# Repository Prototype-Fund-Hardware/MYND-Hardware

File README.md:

# MYND loudspeaker 
This is a community repository (inofficial) for the open hardware of the Teufel loudspeaker MYND: https://teufel.de/mynd-107002004

Due to the file size, the STL files were not uploaded. They can be downloaded directly from the Teufel website: https://docs.teufel.de/download/MYND/open_source.zip

The repository for the firmware can be found here: https://github.com/teufelaudio/mynd-firmware

## License 
CC BY-SA 4.0 Copyright (c) 2025 Lautsprecher Teufel GmbH. 
The corresponding licenses can be found in the CAD and PCB folders.

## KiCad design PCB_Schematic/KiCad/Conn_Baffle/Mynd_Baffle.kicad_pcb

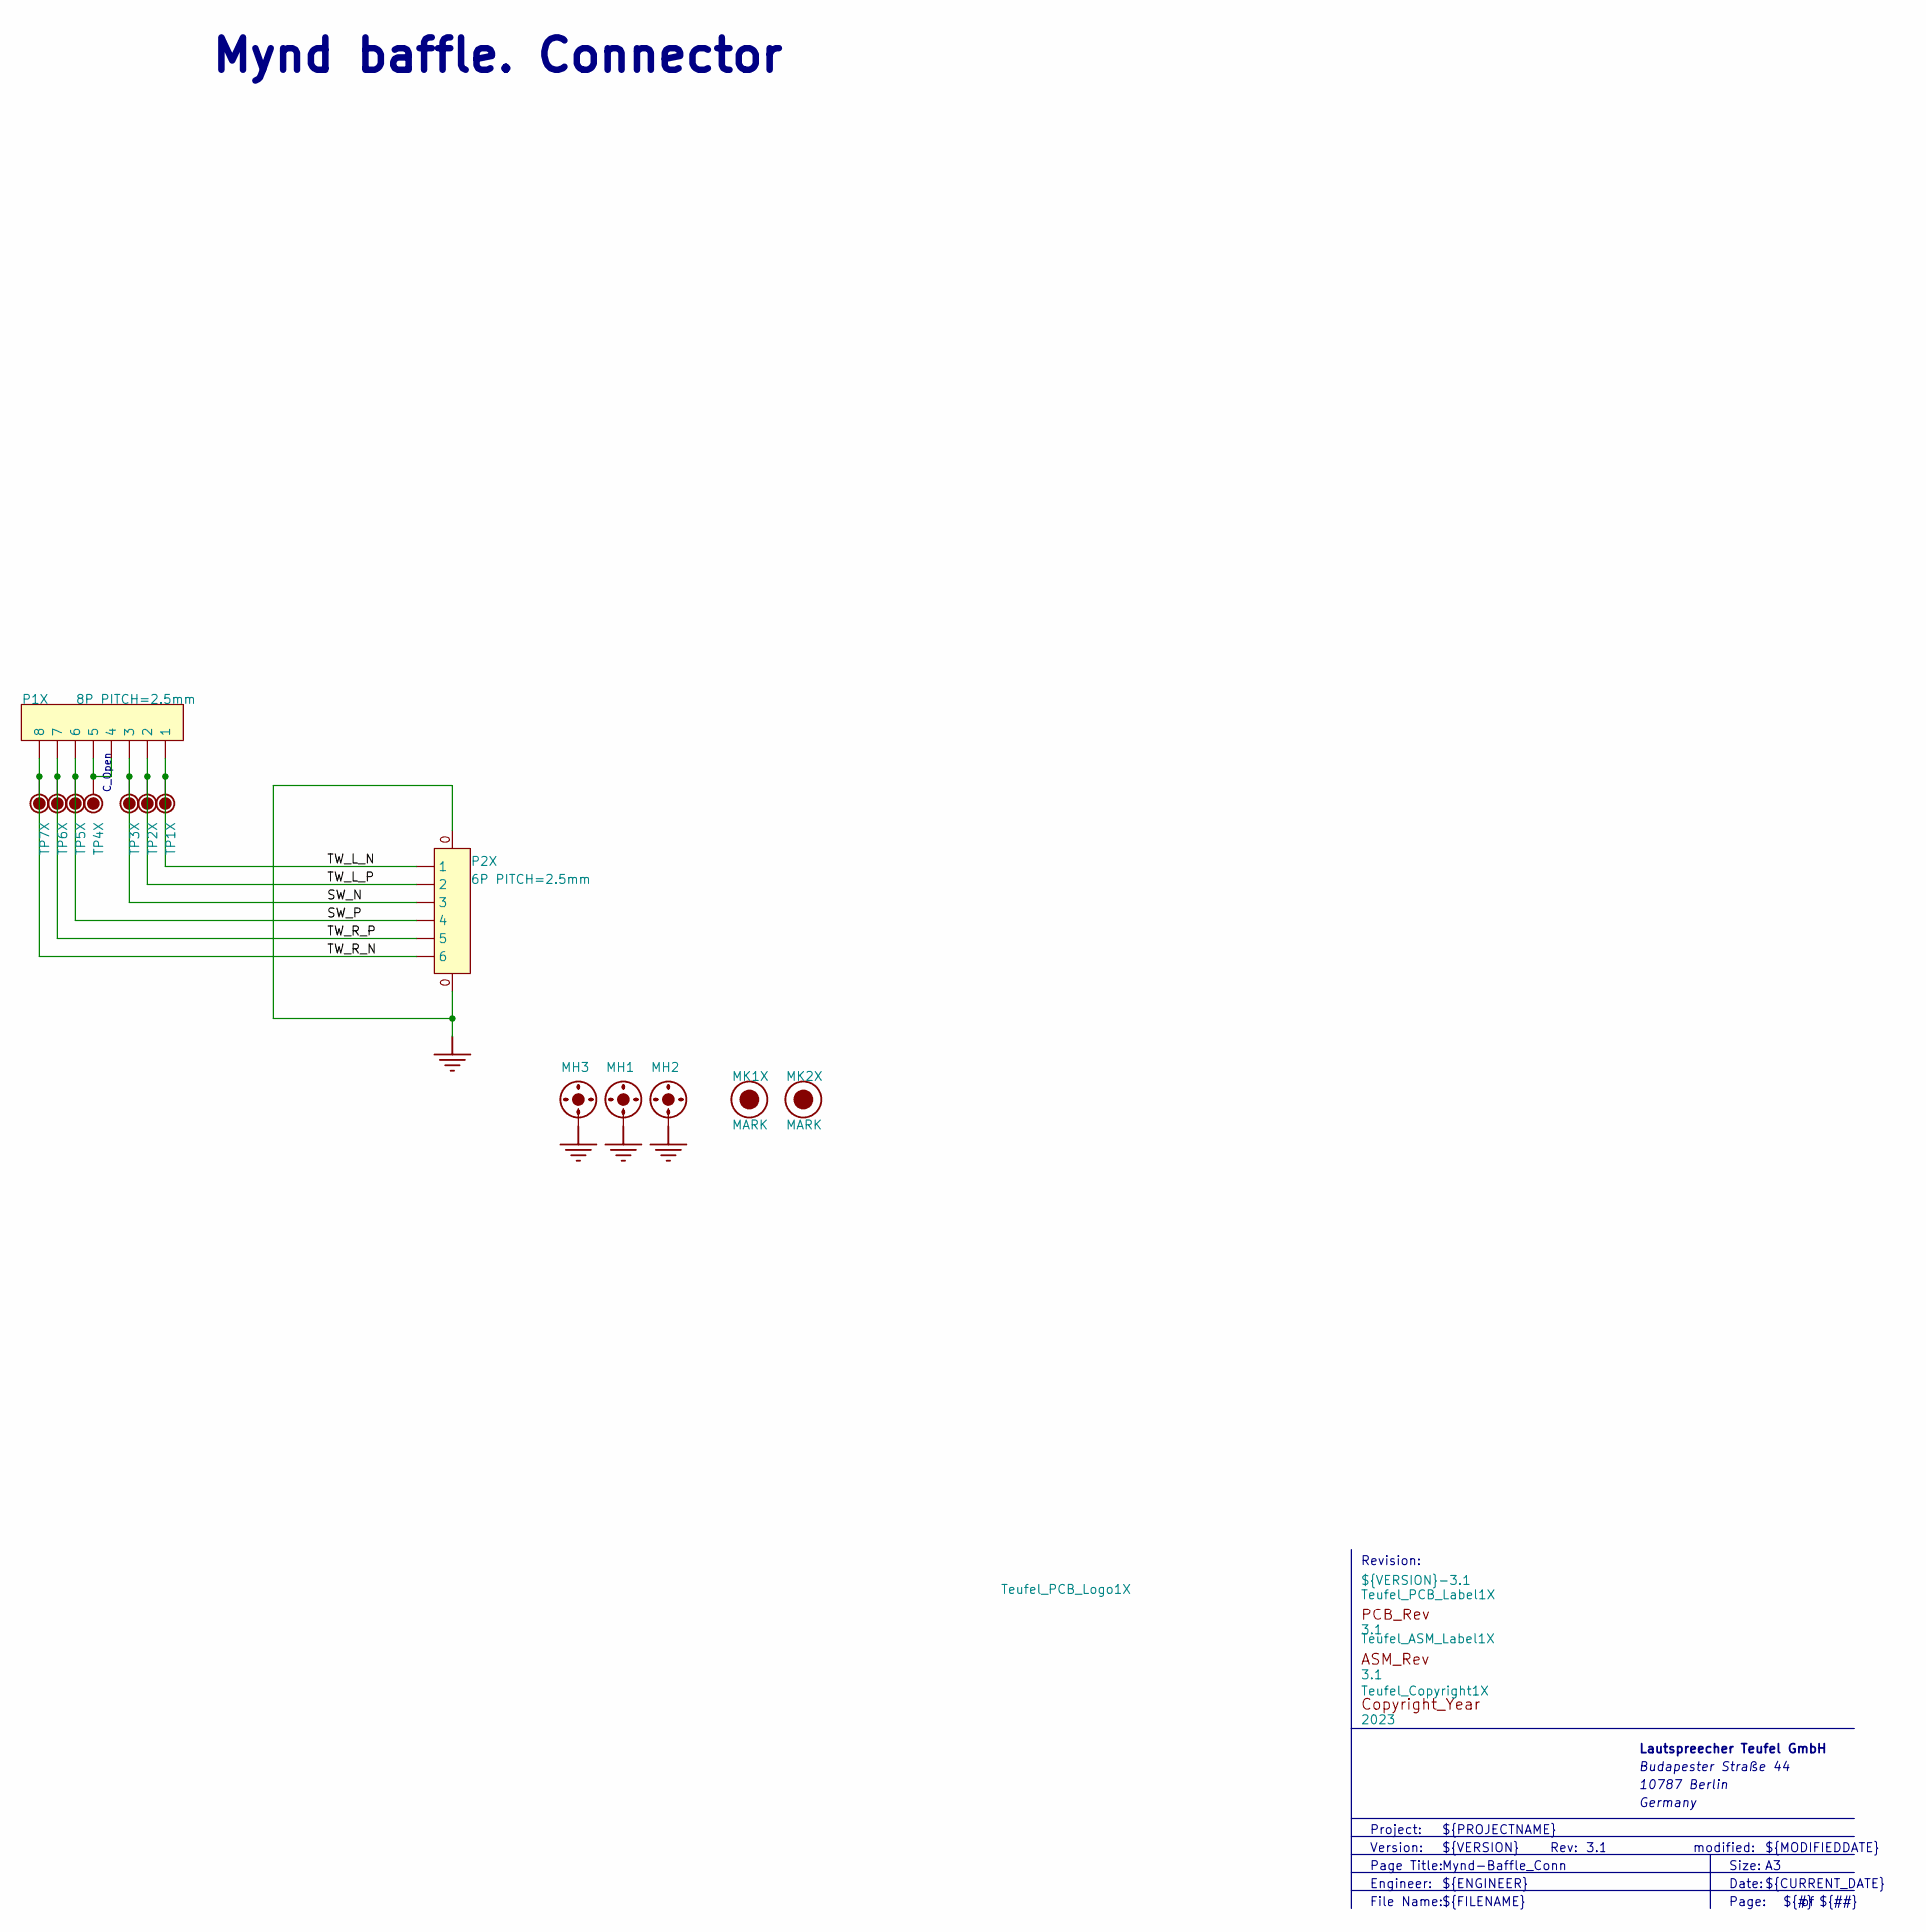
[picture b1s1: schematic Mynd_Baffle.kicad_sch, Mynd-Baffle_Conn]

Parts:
MH1, MH3: SCREW_HOLE_D35; SCREW_D35
MH2: HOLD_D35
MK1X, MK2X: MARK
P1X: 8P PITCH=2.5mm; TSB1_05282; PART_NUMBER 8P PITCH=2.5mm
P2X: 6P PITCH=2.5mm; CON_250_SMD_V_6P; PART_NUMBER 6P PITCH=2.5mm
TP1X, TP2X, TP3X, TP4X, TP5X, TP6X, TP7X: TP12; TP120
Teufel_ASM_Label1X: 3.1; Teufel_ASM_Rev
Teufel_Copyright1X: 2023; TEUFEL_COPYRIGHT
Teufel_PCB_Label1X: 3.1; Teufel_PCB_Rev
Teufel_PCB_Logo1X: ${VERSION}-${REVISION}; Teufel_NoLogo

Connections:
GND: MH1.1, MH2.1, MH3.1, P2X.0
NetP1X_4: P1X.4, P1X.5, TP4X.1
SW_N: P1X.3, P2X.3, TP3X.1
SW_P: P1X.6, P2X.4, TP5X.1
TW_L_N: P1X.1, P2X.1, TP1X.1
TW_L_P: P1X.2, P2X.2, TP2X.1
TW_R_N: P1X.8, P2X.6, TP7X.1
TW_R_P: P1X.7, P2X.5, TP6X.1

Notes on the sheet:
modified:
C_Open
${CURRENT_DATE}
Mynd baffle. Connector
Version:
Date:
File Name:
Page Title:
${FILENAME}
${MODIFIEDDATE}
Lautspreecher Teufel GmbH
Engineer:
${TITLE}
10787 Berlin
Budapester Straße 44
${##}
${ENGINEER}
Project:
Rev:
${PROJECTNAME}
${REVISION}
${VERSION}
Revision:
${#}
Size:
Page:
Germany

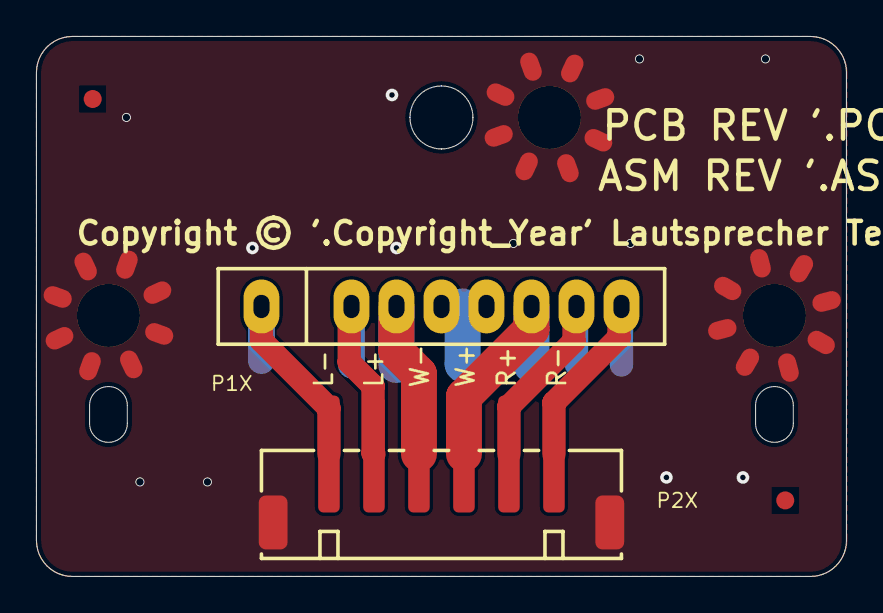
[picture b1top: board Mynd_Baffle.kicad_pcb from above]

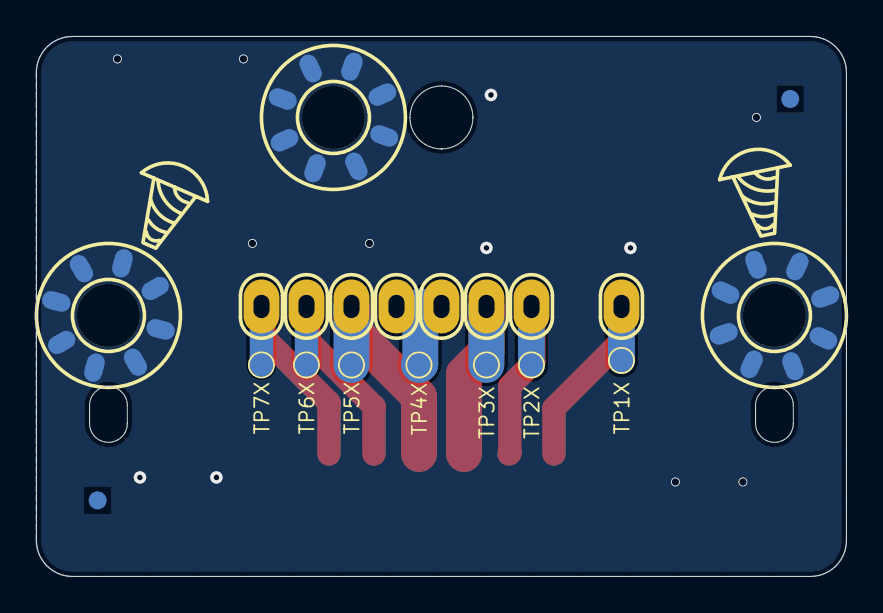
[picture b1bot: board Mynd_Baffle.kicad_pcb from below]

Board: 2 copper layers, 45.0 x 30.0 mm, 18 parts (10 on the bottom side), 8 nets.

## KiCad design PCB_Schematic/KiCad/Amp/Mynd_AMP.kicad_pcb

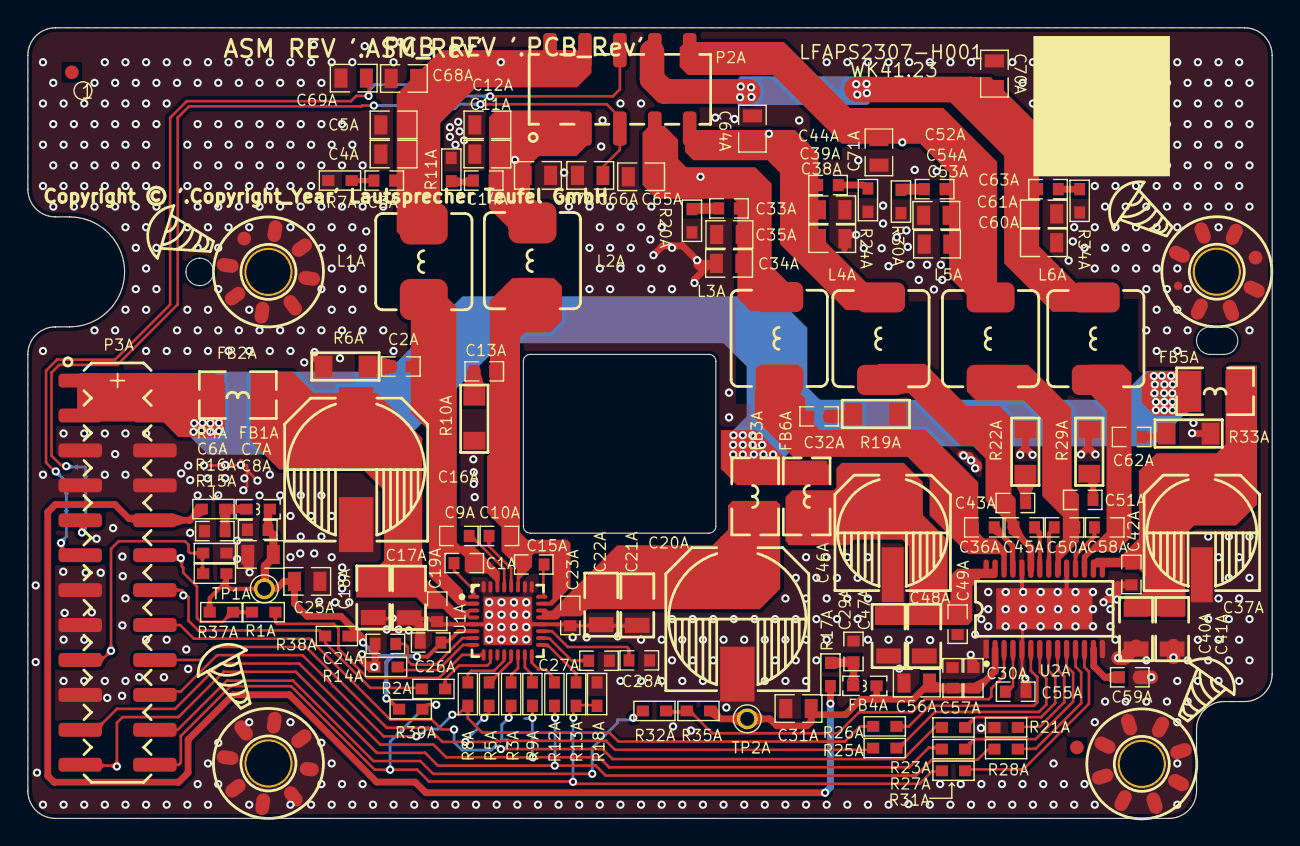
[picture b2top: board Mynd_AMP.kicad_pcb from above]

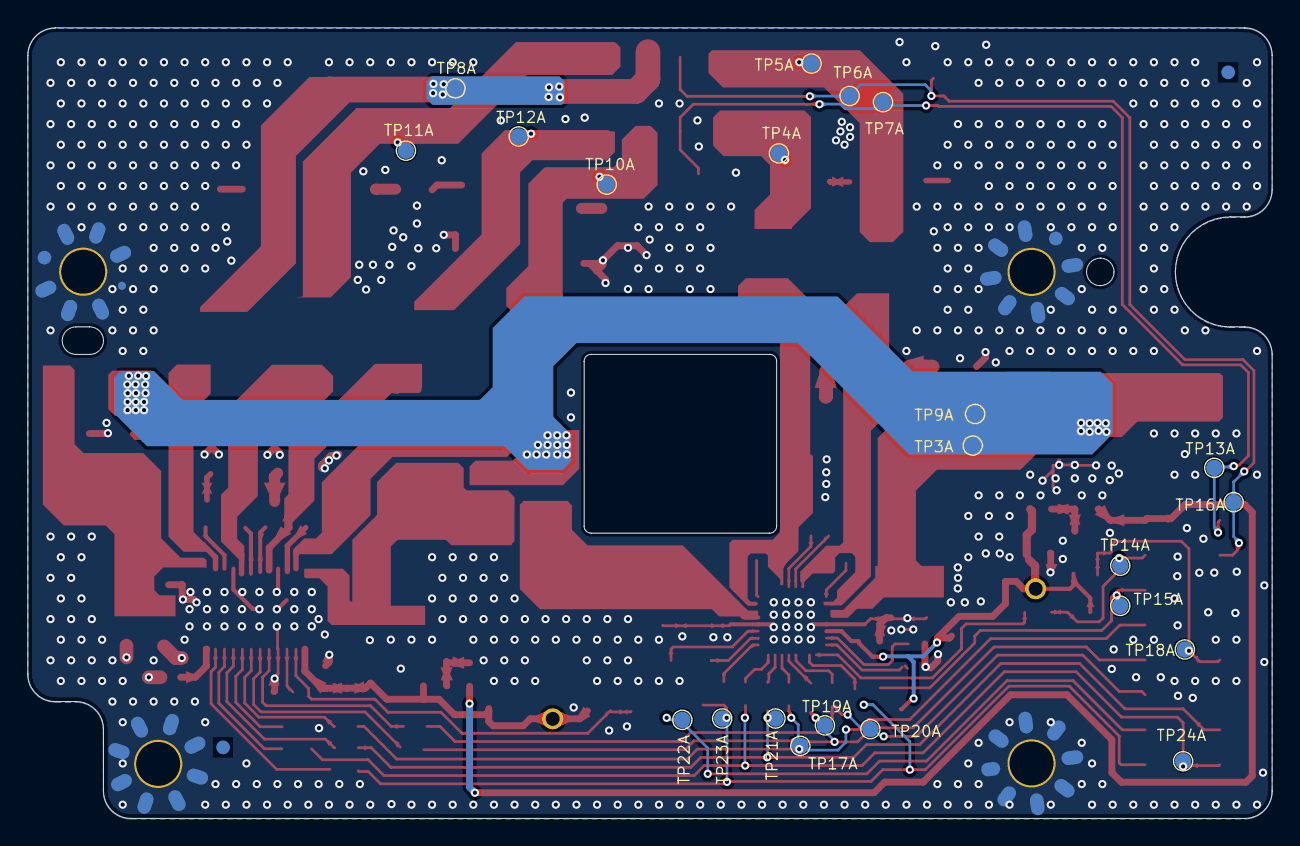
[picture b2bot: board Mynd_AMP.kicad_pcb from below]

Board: 2 copper layers, 90.5 x 57.5 mm, 159 parts (22 on the bottom side), 77 nets.

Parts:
C1A, C9A, C10A, C15A: 470nF; C0603X100
C2A, C13A, C32A, C43A, C51A, C62A: 330pF; C0603X80
C3A, C14A, C33A, C44A, C52A, C63A: 10nF; C0603X100
C4A, C11A: 680nF; C0805_125
C5A, C12A, C35A, C39A, C54A, C61A, C64A, C65A, C66A, C67A, C68A, C69A, C70A, C71A: 1nF; C0805_125
C6A, C7A, C19A, C23A, C26A, C29A, C30A, C42A, C49A, C57A: 100nF; C0603X105
C8A, C31A: 22uF; C0805_145
C16A, C20A: 470uF; ECAP_SMD_1000X1000
C17A, C18A, C21A, C22A, C40A, C41A, C47A, C48A: 10uF; C1206
C24A, C27A, C28A, C55A, C59A: 1uF; C0603X105
C25A, C56A: 4.7uF; C0805_145
C34A, C38A, C53A, C60A: 330nF; C0805_125
C36A, C45A, C50A, C58A: 220nF; C0603X100
C37A, C46A: 220uF; ECAP_SMD_800X1000
FB1A, FB4A: 600R; L0603
FB2A, FB3A, FB5A, FB6A: 56R; L1612
L1A, L2A: 4.7uH; IND_SMD_YT_SQU_L78XW70XH50
L3A, L4A, L5A, L6A: 10uH; IND_SMD_YT_SQU_L78XW70XH30
MH1A, MH2A, MH3A, MH4A: SCREW_HOLE_D32; SCREW_D32
MK_T1A, MK_T2A: MARK
P2A: 2 x 5P 2.54mm; female_2X5_254
P3A: 2 x 12P 2.54mm; Pin_Header_SMD_2X12_254
R1A, R2A, R13A, R31A, R32A: 10R; R0603
R3A, R5A, R8A, R9A, R12A, R14A, R23A, R25A, R26A, R27A, R28A: 0R; R0603
R4A, R17A: 2.2R; R0603
R6A, R10A, R19A, R22A, R29A, R33A: 10R; R1206
R7A, R11A, R20A, R24A, R30A, R34A: 3.3R; R0603
R15A: 100k; R0603
R16A, R18A, R21A, R37A, R38A: 10k; R0603
R35A: 4.7k; R0603
R39A: NC; R0603
TP1A, TP2A: TP_T_60_40
TP3A, TP4A, TP5A, TP6A, TP7A, TP8A, TP9A, TP10A, TP11A, TP12A, TP13A, TP14A, TP15A, TP16A, TP17A, TP18A, TP19A, TP20A, TP21A, TP22A, TP23A, TP24A: TP12; TP120
Teufel_ASM_Label1A: =Comment/Name; Teufel_ASM_Rev
Teufel_Copyright1A: =Comment/Name; TEUFEL_COPYRIGHT
Teufel_PCB_Label1A: =Comment/Name; Teufel_PCB_Rev
Teufel_PCB_Logo1A: T.3.0.0040-2.1; Teufel_NoLogo
U1A: TAS5825PRHBR; QFN32_500X500X100_50_P350X350
U2A: TAS5805MPWPR; TSSOP28(PWP)

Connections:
3V3_STB: P3A.10, R4A.2, R17A.2
3V3_SW: C7A.1, C8A.1, C25A.1, C26A.1, FB1A.2, R15A.1, R37A.1, R38A.1, R39A.1, TP1A.1, U1A.6
3V3_TW: C30A.1, C31A.1, C56A.1, C57A.1, FB4A.2, R35A.1, TP2A.1, U2A.2
24V: FB2A.1, FB3A.1, FB5A.1, FB6A.2, P3A.1, P3A.2, P3A.3, P3A.4, TP3A.1, TP9A.1
Amp_Ver: P3A.17, R15A.2, R16A.1, TP18A.1
BatVCC: C66A.1, P2A.5, P3A.9, TP7A.1, TP13A.1
C_Open: C69A.1, P2A.6, P3A.11, TP6A.1, TP16A.1
Env_Track: P3A.14, R2A.2, R38A.2, TP15A.1
GND: C4A.2, C5A.2, C6A.2, C7A.2, C8A.2, C11A.2, C12A.2, C16A.2, C17A.2, C18A.2, C19A.2, C20A.2, C21A.2, C22A.2, C23A.2, C24A.1, C25A.2, C26A.2, C27A.1, C28A.1, C29A.2, C30A.2, C31A.2, C34A.2, C35A.2, C37A.2, C38A.2, C39A.2, C40A.2, C41A.2, C42A.2, C46A.2, C47A.2, C48A.2, C49A.2, C53A.2, C54A.2, C55A.1, C56A.2, C57A.2, C59A.1, C60A.2, C61A.2, C64A.2, C65A.2, C66A.2, C67A.2, C68A.2, C69A.2, C70A.2, C71A.2, MH1A.1, MH2A.1, MH3A.1, MH4A.1, P3A.5, P3A.6, P3A.7, P3A.8, P3A.13, P3A.15, P3A.19, R6A.2, R7A.2, R10A.1, R11A.2, R14A.1, R16A.2, R18A.2, R19A.2, R20A.2, R21A.2, R22A.1, R24A.2, R29A.2, R30A.2, R33A.1, R34A.2, U1A.0, U1A.5, U1A.20, U1A.25, U1A.26, U1A.31, U1A.32, U2A.0, U2A.1, U2A.5, U2A.14, U2A.19, U2A.24
I2S_BCLK: P3A.18, R5A.1, R25A.1, TP19A.1
I2S_DATA: P3A.16, R3A.1, R23A.1, TP17A.1
I2S_LRCK: P3A.20, R8A.1, R26A.1, TP20A.1
NetC1A_1: C1A.1, C2A.2, C9A.2, L1A.1, U1A.2, U1A.30
NetC1A_2: C1A.2, U1A.1
NetC2A_1: C2A.1, R6A.1
NetC3A_2: C3A.2, R7A.1
NetC6A_1: C6A.1, FB1A.1, R4A.1
NetC9A_1: C9A.1, U1A.29
NetC10A_1: C10A.1, C13A.1, C15A.2, L2A.1, U1A.23, U1A.27
NetC10A_2: C10A.2, U1A.28
NetC13A_2: C13A.2, R10A.2
NetC14A_1: C14A.1, R11A.1
NetC15A_1: C15A.1, U1A.24
NetC16A_1: C16A.1, C17A.1, C18A.1, C19A.1, FB2A.2, U1A.3, U1A.4
NetC20A_1: C20A.1, C21A.1, C22A.1, C23A.1, FB3A.2, U1A.21, U1A.22
NetC24A_2: C24A.2, U1A.7
NetC27A_2: C27A.2, U1A.18
NetC28A_2: C28A.2, U1A.19
NetC29A_1: C29A.1, FB4A.1, R17A.1
NetC32A_1: C32A.1, R19A.1
NetC32A_2: C32A.2, C36A.1, L3A.1, U2A.26
NetC33A_2: C33A.2, R20A.1
NetC36A_2: C36A.2, U2A.25
NetC37A_1: C37A.1, C40A.1, C41A.1, C42A.1, FB5A.2, U2A.15, U2A.16
NetC43A_1: C43A.1, C45A.2, L4A.1, U2A.23
NetC43A_2: C43A.2, R22A.2
NetC44A_1: C44A.1, R24A.1
NetC45A_1: C45A.1, U2A.22
NetC46A_1: C46A.1, C47A.1, C48A.1, C49A.1, FB6A.1, U2A.27, U2A.28
NetC50A_1: C50A.1, C51A.2, L5A.1, U2A.20
NetC50A_2: C50A.2, U2A.21
NetC51A_1: C51A.1, R29A.1
NetC52A_2: C52A.2, R30A.1
NetC55A_2: C55A.2, U2A.4
NetC58A_1: C58A.1, U2A.18
NetC58A_2: C58A.2, C62A.1, L6A.1, U2A.17
NetC59A_2: C59A.2, U2A.13
NetC62A_2: C62A.2, R33A.2
NetC63A_1: C63A.1, R34A.1
NetR1A_1: R1A.1, U1A.9
NetR2A_1: R2A.1, U1A.10
NetR3A_2: R3A.2, U1A.14
NetR5A_2: R5A.2, U1A.13
NetR8A_2: R8A.2, U1A.12
NetR9A_2: R9A.2, U1A.15
NetR12A_2: R12A.2, U1A.16
NetR13A_1: R13A.1, U1A.17
NetR14A_2: R14A.2, U1A.8
NetR21A_1: R21A.1, U2A.9
NetR23A_2: R23A.2, U2A.8
NetR25A_2: R25A.2, U2A.7
NetR26A_2: R26A.2, U2A.6
NetR27A_2: R27A.2, U2A.10
NetR28A_2: R28A.2, U2A.11
NetR31A_1: R31A.1, U2A.12
NetR32A_1: R32A.1, R35A.2, U2A.3
SCL: P3A.23, R12A.1, R28A.1, TP24A.1
SDA: P3A.21, R9A.1, R27A.1, TP21A.1
SW_N: C11A.1, C12A.1, C14A.2, C67A.1, L2A.2, P2A.1, P2A.3, TP4A.1
SW_P: C3A.1, C4A.1, C5A.1, C68A.1, L1A.2, P2A.2, P2A.4, TP5A.1
TW_L_N: C52A.1, C53A.1, C54A.1, C71A.1, L5A.2, P2A.10, TP11A.1
TW_L_P: C60A.1, C61A.1, C63A.2, C70A.1, L6A.2, P2A.8, TP8A.1
TW_R_N: C38A.1, C39A.1, C44A.2, C64A.1, L4A.2, P2A.9, TP12A.1
TW_R_P: C33A.1, C34A.1, C35A.1, C65A.1, L3A.2, P2A.7, TP10A.1
~Amp_PDN: P3A.24, R13A.2, R18A.1, R31A.2, R39A.2, TP23A.1
~Amp_SwFlt: P3A.12, R1A.2, R37A.2, TP14A.1
~Amp_TwFlt: P3A.22, R32A.2, TP22A.1

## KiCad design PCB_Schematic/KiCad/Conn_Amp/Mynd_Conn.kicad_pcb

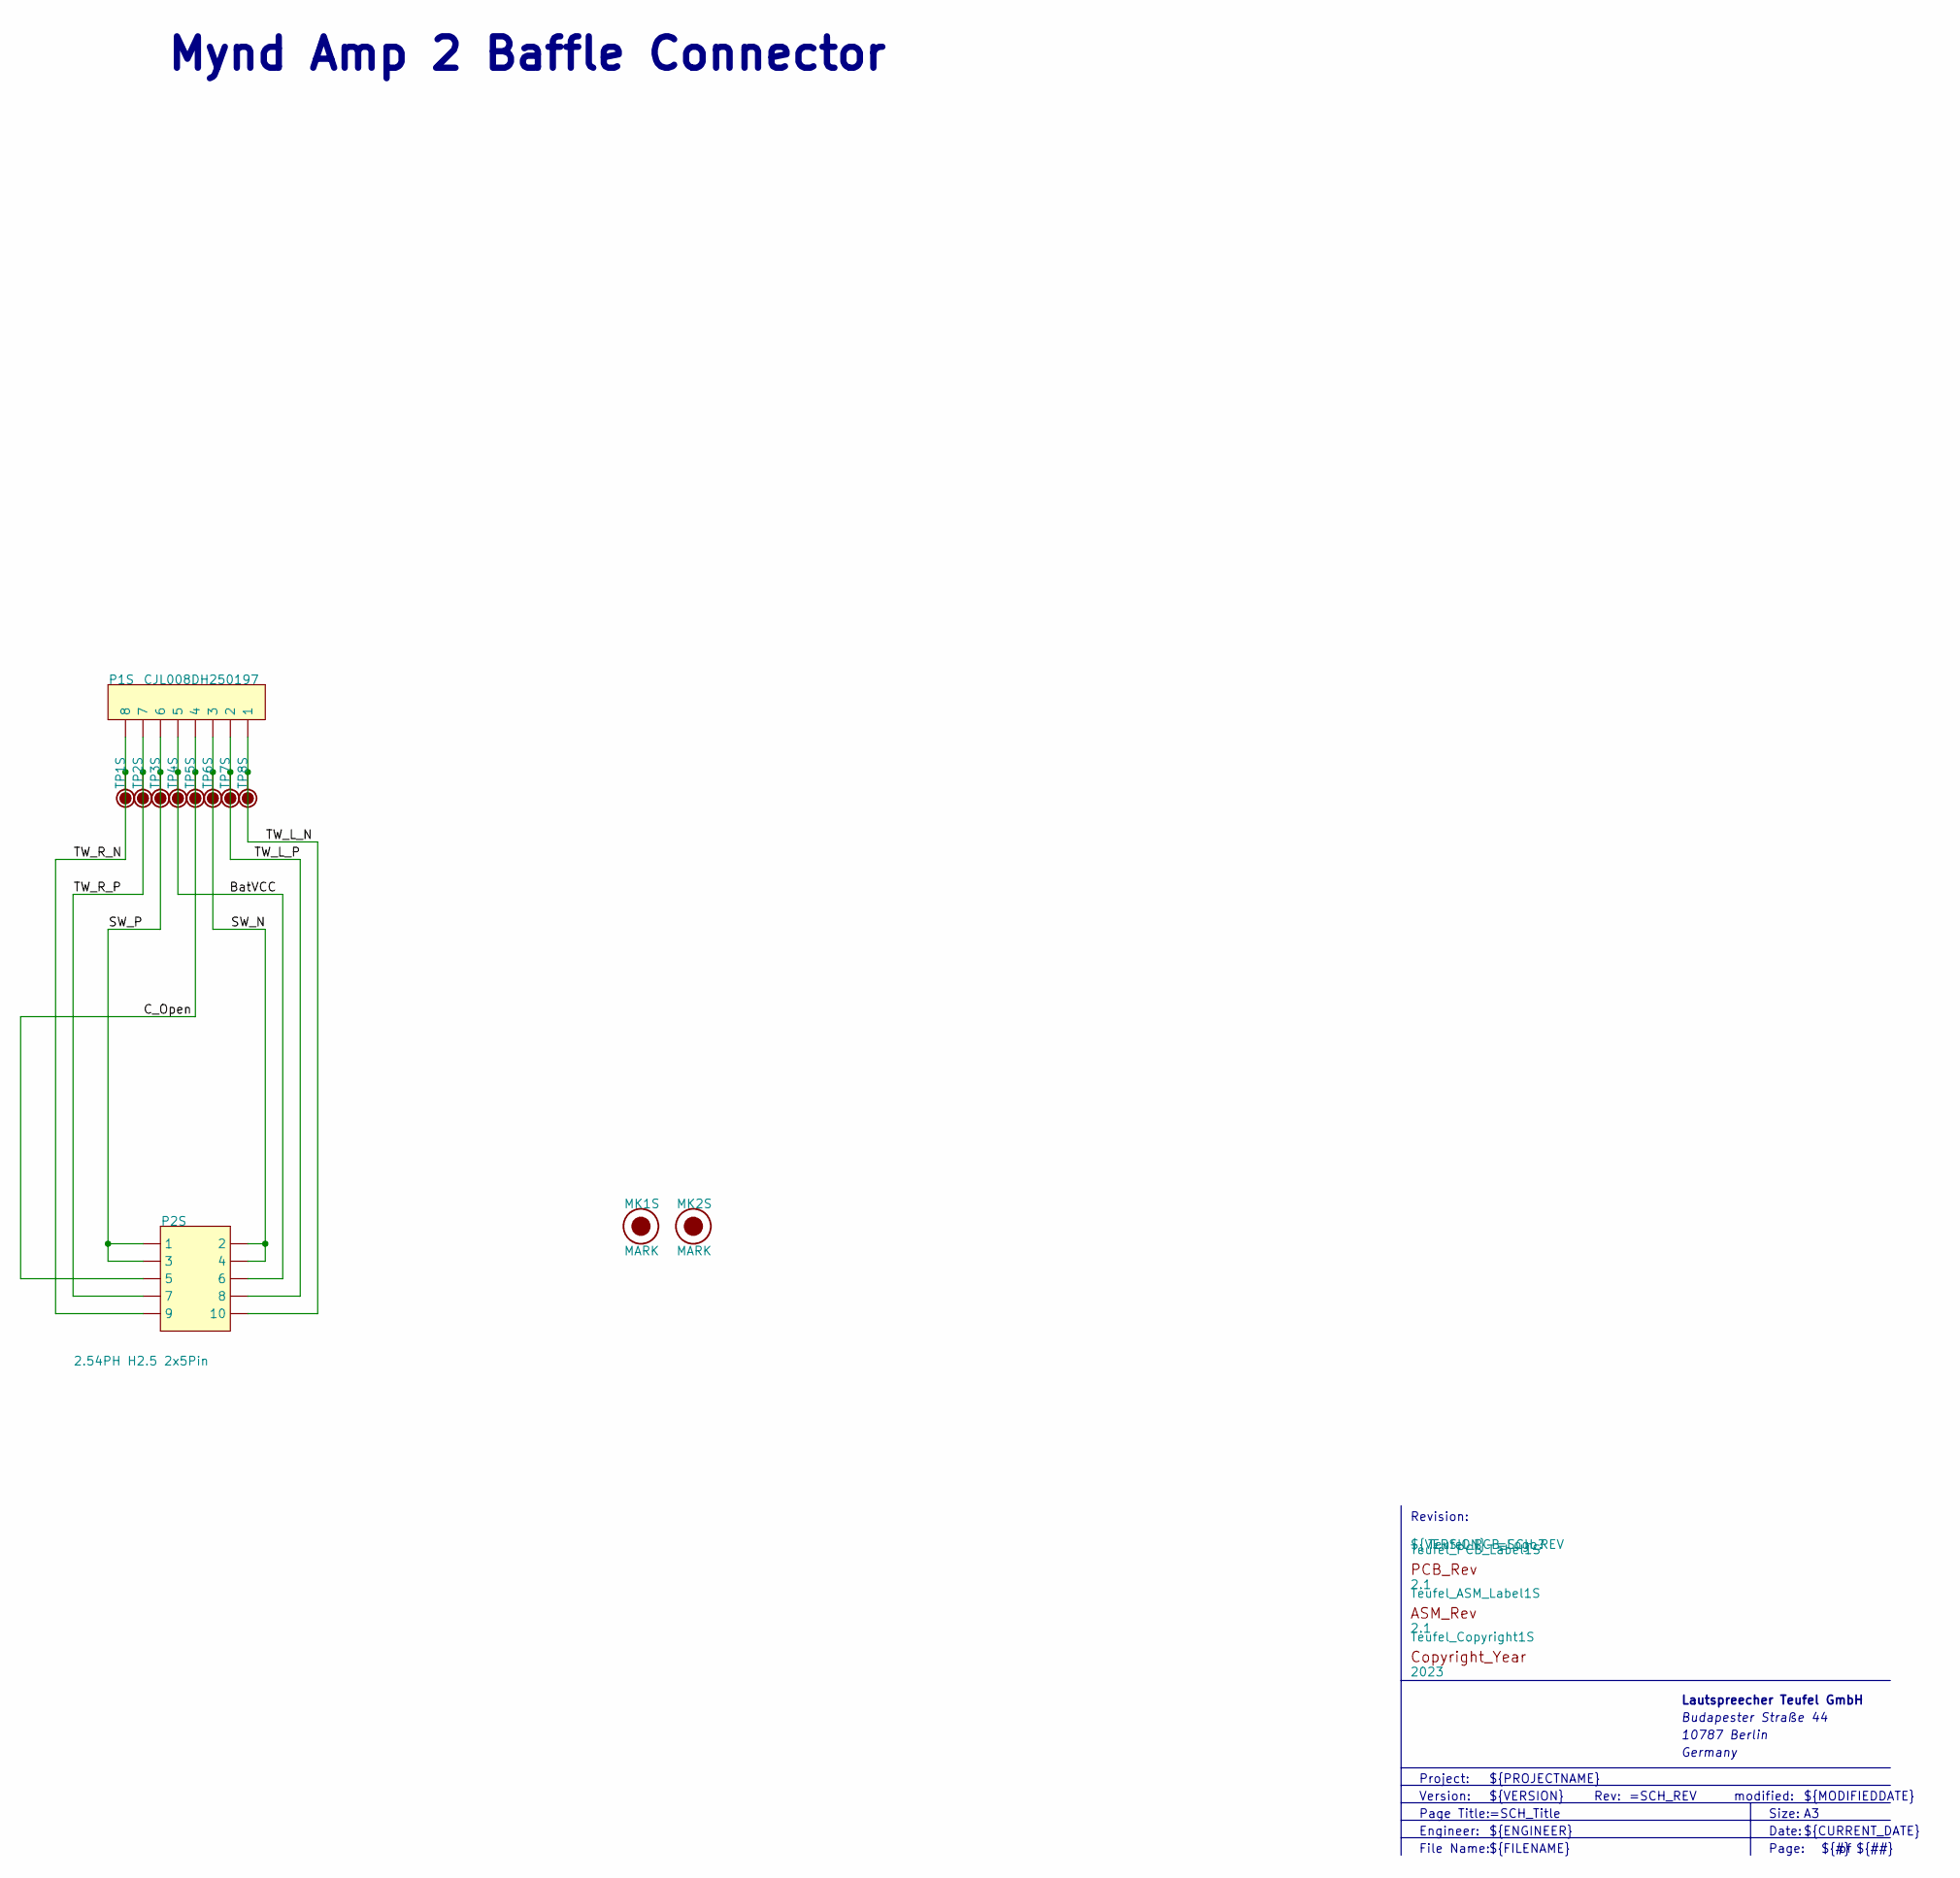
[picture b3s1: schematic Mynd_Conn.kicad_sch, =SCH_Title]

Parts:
MK1S, MK2S: MARK
P1S: CJL008DH250197; PART_NUMBER CJL008DH250197
P2S: 2.54PH H2.5 2x5Pin; Pin_Header_SMD_Side_2X5_254; PART_NUMBER 2.54PH H2.5 2x5Pin
TP1S, TP2S, TP3S, TP4S, TP5S, TP6S, TP7S, TP8S: TP12; TP120
Teufel_ASM_Label1S: 2.1; Teufel_ASM_Rev
Teufel_Copyright1S: 2023; Teufel_Copyright
Teufel_PCB_Label1S: 2.1; Teufel_PCB_Rev

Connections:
BatVCC: P1S.5, P2S.6, TP4S.1
C_Open: P1S.4, P2S.5, TP5S.1
SW_N: P1S.3, P2S.2, P2S.4, TP6S.1
SW_P: P1S.6, P2S.1, P2S.3, TP3S.1
TW_L_N: P1S.1, P2S.10, TP8S.1
TW_L_P: P1S.2, P2S.8, TP7S.1
TW_R_N: P1S.8, P2S.9, TP1S.1
TW_R_P: P1S.7, P2S.7, TP2S.1

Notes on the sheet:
Mynd Amp 2 Baffle Connector
${FILENAME}
Date:
Version:
Germany
Size:
Page Title:
${PROJECTNAME}
Lautspreecher Teufel GmbH
modified:
Budapester Straße 44
${REVISION}
${MODIFIEDDATE}
Revision:
Project:
${#}
Rev:
${ENGINEER}
File Name:
${CURRENT_DATE}
${VERSION}
Page:
${##}
Engineer:
${TITLE}
10787 Berlin

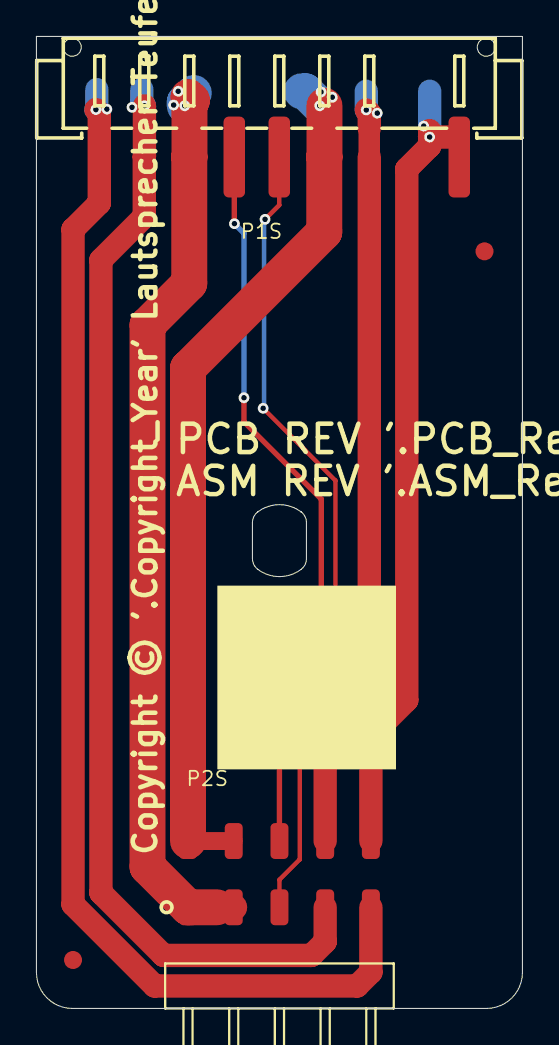
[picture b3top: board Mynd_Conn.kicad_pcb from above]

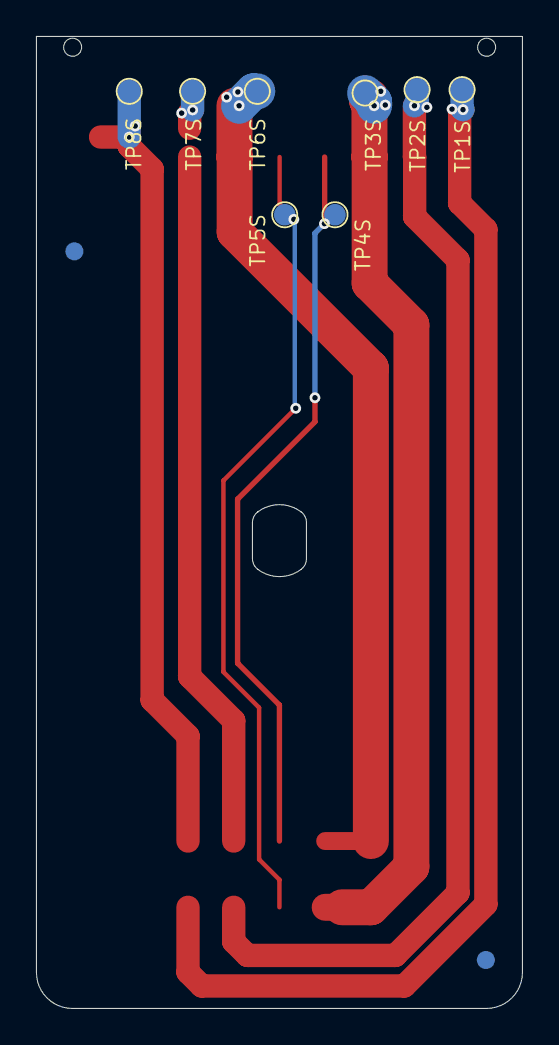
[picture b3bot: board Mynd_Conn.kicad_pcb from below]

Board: 2 copper layers, 27.0 x 54.0 mm, 16 parts (8 on the bottom side), 8 nets.

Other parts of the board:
Teufel_PCB_Logo?: T.3.0.0040-2.1; Teufel_NoLogo

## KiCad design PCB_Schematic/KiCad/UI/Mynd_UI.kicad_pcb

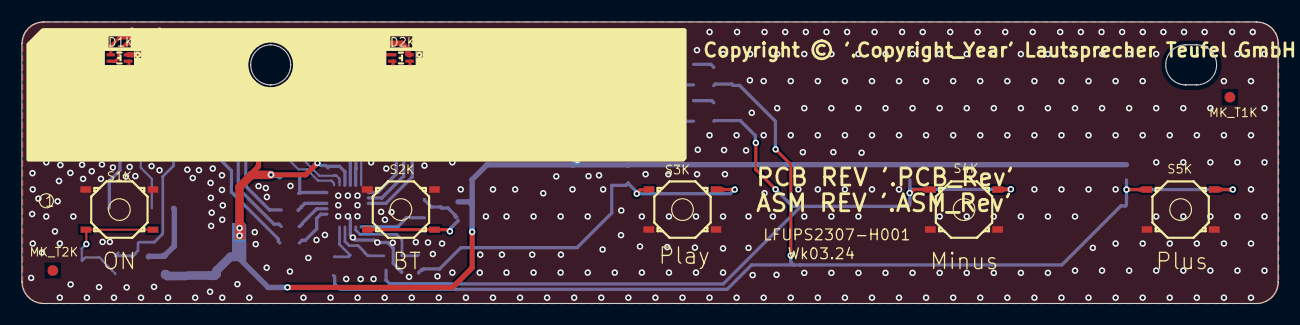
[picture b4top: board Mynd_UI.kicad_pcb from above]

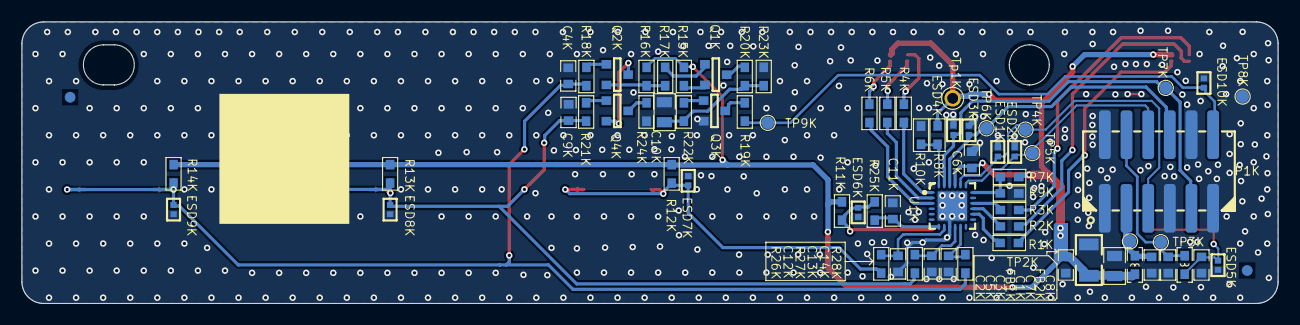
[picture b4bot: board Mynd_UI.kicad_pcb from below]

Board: 2 copper layers, 116.0 x 26.0 mm, 82 parts (69 on the bottom side), 43 nets.

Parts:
C1K, C2K, C4K, C6K, C9K: 100nF; C0603X100
C3K, C10K: 10uF; C0805_145
C5K: 22uF; C1206
C7K, C8K: 33pF; C0603X80
C11K, C12K, C13K, C14K: NC; C0603X100
D1K, D2K: JH-CRGBB06GTP014; LED_SMD_F_T_160X80X60
ESD1K, ESD2K, ESD3K, ESD4K, ESD6K, ESD7K, ESD8K, ESD9K, ESD10K: CESD0501CU; DFN2_100X60X50_65
ESD5K: BDFN2C121V; DFN2_100X60X50_65
FB1K, FB2K: 600R; L0603
MK_T1K, MK_T2K: MARK
P1K: WB200AL-12; WB200AL_2x6P
Q1K, Q2K, Q4K: CJ3401; SOT23-GSD
Q3K: 2N7002K; SOT23-GSD
R1K, R2K, R5K, R6K: 22R; R0603
R3K, R4K: 75R; R0603
R7K, R8K: 100R; R0603
R9K, R10K, R16K, R22K: 10k; R0603
R11K, R12K, R13K, R14K: 100k; R0603
R15K, R24K: 0R; R0603
R17K: 4.7k; R0603
R18K, R21K: 150k; R0603
R19K: 10R; R0603
R20K: 680k; R0603
R23K: 1M; R0603
R25K, R26K, R27K, R28K: 1k; R0603
S1K, S2K, S3K, S4K, S5K: TC-1316A-H1.5-180GF; TACT_SW_SMD_52X52X15
TP2K, TP3K, TP4K, TP5K, TP6K, TP7K, TP8K, TP9K: TP12; TP120
Teufel_ASM_Label1K: =Comment/Name; Teufel_ASM_Rev
Teufel_Copyright1K: =Comment/Name; TEUFEL_COPYRIGHT
Teufel_PCB_Label1K: =Comment/Name; Teufel_PCB_Rev
Teufel_PCB_Logo1K: T.3.0.0040-3.2; Teufel_NoLogo
Tp1K: TP_T_60_40
U1K: AW9523BTQR; QFN24_400X400X100_50_P270X270

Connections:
3V3_LED: C2K.1, C3K.1, C5K.2, C6K.2, D1K.C, D2K.C, FB1K.1, R7K.2, R8K.2, R11K.1, R12K.1, R13K.1, R14K.1, R15K.1, R16K.2, Tp1K.1, U1K.21
3V3_STB: C1K.1, FB1K.2, P1K.3, TP2K.1
Btn_BT: ESD6K.2, R11K.2, R25K.2, S2K.3, S2K.4
Btn_Minus: C9K.1, ESD8K.2, R13K.2, R21K.1, R27K.2, S4K.3, S4K.4
Btn_On: C8K.1, ESD5K.2, FB2K.2, S1K.3, S1K.4
Btn_Play: ESD7K.2, R12K.2, R26K.2, S3K.3, S3K.4
Btn_Plus: C4K.1, ESD9K.2, R14K.2, R18K.1, R28K.2, S5K.3, S5K.4
GND: C1K.2, C2K.2, C3K.2, C4K.2, C5K.1, C6K.1, C7K.2, C8K.2, C9K.2, C10K.2, C11K.2, C12K.2, C13K.2, C14K.2, ESD1K.1, ESD2K.1, ESD3K.1, ESD4K.1, ESD5K.1, ESD6K.1, ESD7K.1, ESD8K.1, ESD9K.1, ESD10K.1, P1K.1, P1K.2, P1K.7, P1K.10, P1K.11, Q3K.S, R9K.2, R10K.2, R23K.1, R24K.1, S1K.1, S1K.2, S2K.1, S2K.2, S3K.1, S3K.2, S4K.1, S4K.2, S5K.1, S5K.2, TP8K.1, U1K.0, U1K.9
I2C2_SCL: ESD2K.2, P1K.6, TP5K.1, U1K.19
I2C2_SDA: ESD1K.2, P1K.5, TP4K.1, U1K.20
MCU_RST: ESD10K.2, P1K.12, R19K.1, TP9K.1
NetC10K_1: C10K.1, R20K.2, R22K.1, R23K.2
NetC11K_1: C11K.1, R25K.1, U1K.7
NetC12K_1: C12K.1, R26K.1, U1K.8
NetC13K_1: C13K.1, R27K.1, U1K.10
NetC14K_1: C14K.1, R28K.1, U1K.11
NetD1K_B: D1K.B, R1K.1
NetD1K_G: D1K.G, R2K.1
NetD1K_R: D1K.R, R3K.1
NetD2K_B: D2K.B, R6K.1
NetD2K_G: D2K.G, R5K.1
NetD2K_R: D2K.R, R4K.1
NetQ1K_D: Q1K.D, R20K.1
NetQ1K_G: Q1K.G, R17K.2
NetQ1K_S: Q1K.S, R15K.2
NetQ2K_D: Q2K.D, Q4K.S
NetQ2K_G: Q2K.G, R18K.2
NetQ2K_S: Q2K.S, R16K.1, R17K.1
NetQ3K_D: Q3K.D, R19K.2
NetQ3K_G: Q3K.G, R22K.2
NetQ4K_D: Q4K.D, R24K.2
NetQ4K_G: Q4K.G, R21K.2
NetR1K_2: R1K.2, U1K.14
NetR2K_2: R2K.2, U1K.15
NetR3K_2: R3K.2, U1K.16
NetR4K_2: R4K.2, U1K.1
NetR5K_2: R5K.2, U1K.2
NetR6K_2: R6K.2, U1K.3
NetR7K_1: R7K.1, R9K.1, U1K.18
NetR8K_1: R8K.1, R10K.1, U1K.24
\P_Btn: C7K.1, FB2K.1, P1K.4, TP3K.1
\UI_Int: ESD3K.2, P1K.8, TP6K.1, U1K.22
\UI_Rst: ESD4K.2, P1K.9, TP7K.1, U1K.23

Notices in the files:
parts and their libraries:
Copyright © '.Copyright_Year' Lautsprecher Teufel GmbH
Teufel Copyright PCB Label
